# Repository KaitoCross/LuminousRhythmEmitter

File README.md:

# Future Gadget #16: Luminous Rhythm Emitter

## DIY Penlight project

### Description

This project is a work in progress! Use and build at your own risk! No guarantees given. Parts of the current version may be untested.
This project aims to create an open-source homemade penlight for various concerts (J-Pop, Idols, VTuber, Vocaloid) that can be controlled remotely. You'll need access to a 3D printer and equipment for soldering SMD parts. You'll have to order a PCB, based on the KiCad design provided in the `Circuits` folder, as well as some electronic parts. The `3D` folder contains the stl files for 3D printing. A parts list is located in the `Circuits` folder.

### Setup

[A brief How-To is located in `Circuits`](Circuits/README.md)

### Current Features

- Rechargable via USB-C
- Manual selection of LED color by pressing the button (cycling though a preset with 12 colors)
- Setting the color via (unsecured) Bluetooth Low Energy
- Separate Power Off switch

### Shoutouts

Shoutouts to:

- rico132 (for helping with Fusion 360 and helping in fixing electronics)
- CaptainMeow (for the Otomo drawing on the PCB design)
- Dominik K (brainstormed the idea with me)
- KFP & the general VTubing community

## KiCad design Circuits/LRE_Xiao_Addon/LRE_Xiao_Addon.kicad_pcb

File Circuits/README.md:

# Hardware List:

- Seeed Studio XIAO ESP32C3
- power switch: MFP 120 by Knitter-Switch
- Any 18350 Li-ion battery with a **protection circuit** (preventing deep discharge)
- Button: generic 6x6x5mm pushbutton
- ~~20mm ø LED Lens (60°), max 11mm high~~
- screw the lens actually, it's better without
- The custom printed PCB
  - I recommend ordering the custom PCB through JLCPCB
- 2x 6-Pin 2.54mm Dupont female pin header (socket 8,5mm high)
- 2x 6-Pin 2.54mm Dupont male pin header (pin 6mm high)
- If PCB is not pre-assembled:
  - 1x Inolux IN-P55TATRGB
  - 3x S8050 (SMD type SOT-23)
  - SMD type 1206 resistors:
    - 3x 15,5 kOhm (or slightly lower)
    - 2x 11 Ohm (or slightly higher)
    - 1x 61 Ohm (or slightly higher)
- battery contacts (with spring)
- (optional) 100 mm 2,4 Ghz Antenna
- an LED light diffusion filter. Dimensions: 9,5cm x 14,5cm  (15.1mm inner cylinder radius)
  Recommendations: 
  - [Lee Colour Filter 251 (1/4 white diffusion)](https://www.thomann.de/intl/lee_colour_filter_251_q_w_diffus.htm)
  - [Lee Colour Filter 252 (1/8 white diffusion)](https://www.thomann.de/intl/lee_colour_filter_252_e_w_diffus.htm)

# How to Build

You’ll need to familiarize yourself with soldering SMD components.  
Required tools:

- SMD rework station

- Tweezers

- Solder paste and (preferably) no-clean flux

- Regular soldering iron and solder for through-hole parts

- [KiCAD](https://www.kicad.org/) (free & open-source) to open the circuit files

## XIAO ESP32C3

Start with the XIAO ESP32C3. Solder the male 6-pin headers to the board, aligning the 5V with the first pin of the pin header, with the long side of the pins on facing the same direction as the big chip. DO NOT USE 7-PIN headers! Solder the other male pin header exactly in parallel with the first one.s

## Custom PCB

Now you can start soldering the parts to the custom PCB. Start with the SMD parts, soldering them to their designated spots as marked on the board. Once that is done, solder the female pin headers to the board. They need to be on the side opposite to the LED.

## Battery wiring

Solder a red wire to the battery contact without the spring (positive battery pole). Thread the red wire through the centre hole of the 3D-printed battery wall. Then solder the other end of the red wire to the battery contact (positive pole) of the XIAO.

Solder a black wire to the negative battery contact pad of the XIAO. Solder the other end to the centre pin of the power switch. Solder another black wire from one of the outer pins of the power switch to the battery contact with the spring (negative). Ensure that this wire is long enough so that it can hang out of the bottom end (short thread) of the penlight case. Make it \~2 cm longer than the distance between USB port and bottom end.

## Pushbutton wiring

Connect two wires to the J4 holes on the PCB. Connect both wires to the pushbutton, one wire to the top right leg, the other one the the bottom right leg (see example image below)

## Assembly

3D-print all parts in the [`3D` folder](../3D). Print settings recommendations [are also provided.](../3D/print_settings.md) Some cutouts (mainly for the buttons) need to be sanded for a better fit.

Connect the PCB and the XIAO through the pin headers.

[Install the firmware on the XIAO](../Software/README.md) and test it.

Start with the half with the rectangular cutout on the top. Place the PCB on top of the Edge above the cutout, with the USB port facing the cutout. Place the black wire in the recess in the bottom. Then, but the battery wall in the space on the recess, aligning it with said recess, while the positive battery pole faces outward towards the bottom thread. 

To make working with the pushbutton easier, you need to straighten the unused legs, aligning them with the case of the button itself. Now, pull the pushbutton though the D-shaped hole, with the wires facing the wall. Place the button cap on the pushbutton. Put the rectangular power switch into it's holder near the XIAO.

Now, put the ~~lens~~ reflector into the ~~lens~~ reflector holder with the ~~flat~~ open side of the ~~lens~~ reflector facing the small end of the holder. Push it all the way in. Place the ~~lens~~ reflector holder on top of the PCB.

Now put the other half of the penlight base on top and close the case, making sure the buttons fit into the other half as well. Then you can screw on the top part. Into the top part, you can then place your light diffusion filter. You can then close the top part by screwing on the respective cap.

Now, you can place the battery in the battery compartment. Make sure that the positive pole faces inwards. The negative pole then faces outwards, and connects to the spring. hold the spring in place and close the battery compartment with the other, bigger cap.

Now you should be able to power on and use your penlight!

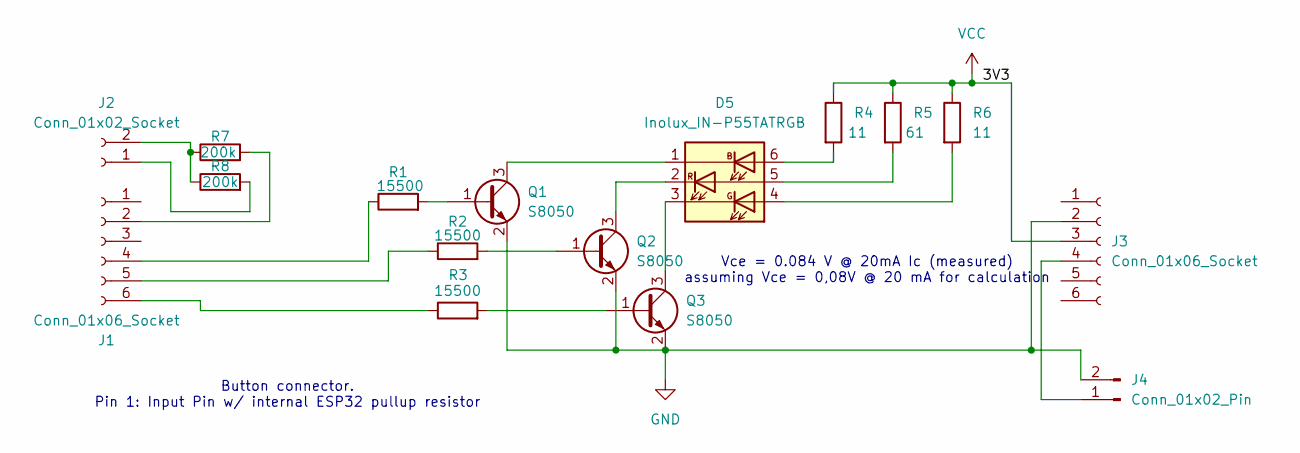
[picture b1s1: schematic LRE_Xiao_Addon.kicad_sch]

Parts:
D5: Inolux_IN-P55TATRGB; LED_Inolux_IN-P55TATRGB_PLCC6_5.0x5.5mm_P1.8mm
J1, J3: Conn_01x06_Socket; PinSocket_1x06_P2.54mm_Vertical
J2: Conn_01x02_Socket; PinHeader_1x02_P2.54mm_Vertical
J4: Conn_01x02_Pin; PinHeader_1x02_P2.54mm_Vertical
Q1, Q2, Q3: S8050; SOT-23
R1, R2, R3: 15500; R_1206_3216Metric_Pad1.30x1.75mm_HandSolder
R4, R6: 11; R_1206_3216Metric_Pad1.30x1.75mm_HandSolder
R5: 61; R_1206_3216Metric_Pad1.30x1.75mm_HandSolder
R7, R8: 200k; R_0805_2012Metric_Pad1.20x1.40mm_HandSolder

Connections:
GND: J3.2, J4.2, Q1.2 (E), Q2.2 (E), Q3.2 (E)
unnamed: D5.6 (AB), R4.2
unnamed: D5.4 (AG), R6.2
unnamed: D5.5 (AR), R5.2
unnamed: D5.1 (KB), Q1.3 (C)
unnamed: D5.3 (KG), Q3.3 (C)
unnamed: D5.2 (KR), Q2.3 (C)
unnamed: J1.2, R7.2
unnamed: J1.4, R1.1
unnamed: J1.5, R2.1
unnamed: J1.6, R3.1
unnamed: J2.1, R8.2
unnamed: J2.2, R7.1, R8.1
unnamed: J3.4, J4.1
unnamed: Q1.1 (B), R1.2
unnamed: Q2.1 (B), R2.2
unnamed: Q3.1 (B), R3.2
VCC: J3.3, R4.1, R5.1, R6.1

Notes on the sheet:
Vce = 0.084 V @ 20mA Ic (measured) assuming Vce = 0,08V @ 20 mA for calculation
Button connector. Pin 1: Input Pin w/ internal ESP32 pullup resistor

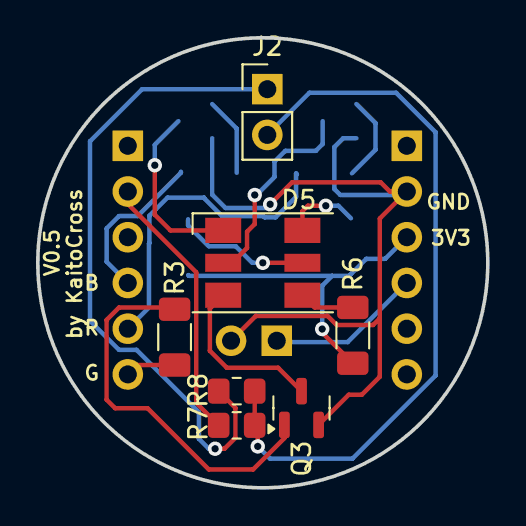
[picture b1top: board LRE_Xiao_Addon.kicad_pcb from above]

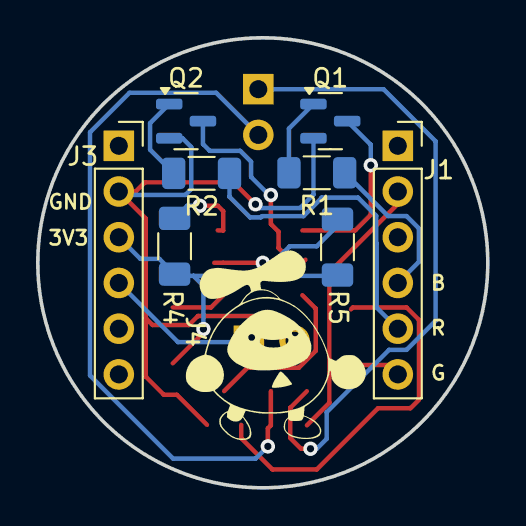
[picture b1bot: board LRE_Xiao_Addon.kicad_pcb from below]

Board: 2 copper layers, 25.0 x 25.0 mm, 16 parts (9 on the bottom side), 18 nets.

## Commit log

2025-07-28 formatting
2025-07-28 software
2025-07-28 add hardware
2025-07-29 updated resistors
2025-08-06 ESPhome config
2025-08-12 USB Port accessible, updated color scheme
2025-08-14 widened button hole & USB port
2025-08-14 fix color wheel, activate LED on startup
2025-08-16 widened top thread for stability
2025-09-23 adjusted hole for power slider
2025-10-07 random update
2025-10-12 PCB update
2025-10-30 Documentation update, Bugfix esphome conf
2025-10-31 Documentation Update
2025-11-01 PCB changes: RGB Pins moved, voltage div to A0 for measuring batt voltage, voltage div to detect VBUS voltage
2025-11-08 added documentation
2025-11-08 Bill of Materials for PCB added
2025-11-08 Documentation + 3D model update
2025-11-08 light balancing
2025-11-09 adjust resistors
2025-11-10 update parts information
2025-11-11 update hardware info
2025-11-14 CAD changes
2025-11-14 cap color recommendation
2025-12-02 replace lens with "reflector"
2025-12-27 bugfix gatttool test
2026-01-06 bugfix firmware
2026-01-06 PCB with batt voltage readings compomnents
2026-01-06 fix the mess by using a backup
2026-01-06 PCB v0.5
2026-01-06 smol fixes
2026-01-06 v0.51
2026-01-14 Add basic Android BLE color control app
2026-01-14 Fix app losing device scans after lifecycle update
2026-01-18 Remove unused background drawable
2026-01-18 Add discovered device status display and saturation slider
2026-01-19 Use dynamic theme
2026-03-06 improved default color palette
